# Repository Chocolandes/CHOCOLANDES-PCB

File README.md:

# CHOCOLANDES-PCB

In this repository you will find the gerber files ready for the Chocolandes PCB fabrication and the eagle files with which the pcb was designed.

Here are the components and connections contained in the instrumentacion.sch file:

## Material's list:
### In this project we use two ESP32 microcontrollers. One is dedicated to the stepper motor movement (ESP-MOT) and the other is in charge of all the other functionalities (ESP-MAIN).
### L293D
Dual DC motor driver 

* In1: D33 ESP-MAIN
* In2: D32 ESP-MAIN
* Out1: Red wire motor pump
* Out2: Black wire motor pump
* En1: 5V
* VCC: 5V
* Vss: 12V
* Pin 4 y 5: GND

### HX711
Load cell ADC converter

* E+: Red
* E-: Black
* A+: Withe
* A-: Green
* Dt: D26 ESP-MAIN
* Sck: D27 ESP-MAIN
* Vcc: 5V

### A4988
Stepper motor driver 
* Dir: D19  ESP-MOT
* Step: D18  ESP-MOT
* Enable: D5  ESP-MOT
* Vdd: 5V
* Reset & Sleep Are connected between them
* 2B: Black 
* 2A: Green
* 1A: Blue
* 1B: Red
* Vmot: External power (12V)

### NEMA 17HS4401s
Stepper motor with 1.8° resolution
* Black: 2B
* Green: 2A
* Blue: 1A
* Red: 1B
### HC020P
* Vdd: 5V
* Data: D34 ESP-MOT
### DS18B20
* Vdd: 5V
* Data: D13 ESP-MAIN
### Motor Pump
* Red: Out1 L293D
* Black: Out2 L293D
### Load Cell
* Red: E+
* Black: E-
* Withe: A+
* Green: A-

### ESP-MAIN
* D33: In1 L293D
* D32: In2 L293D
* D26: Dt HX711
* D27: Sck HX711
* D13: Data DS18B20
### ESP-MOT
* D5: Enable A4988
* D19: DIR A4988
* D18: STEP A4988
* D34: Data HC020P

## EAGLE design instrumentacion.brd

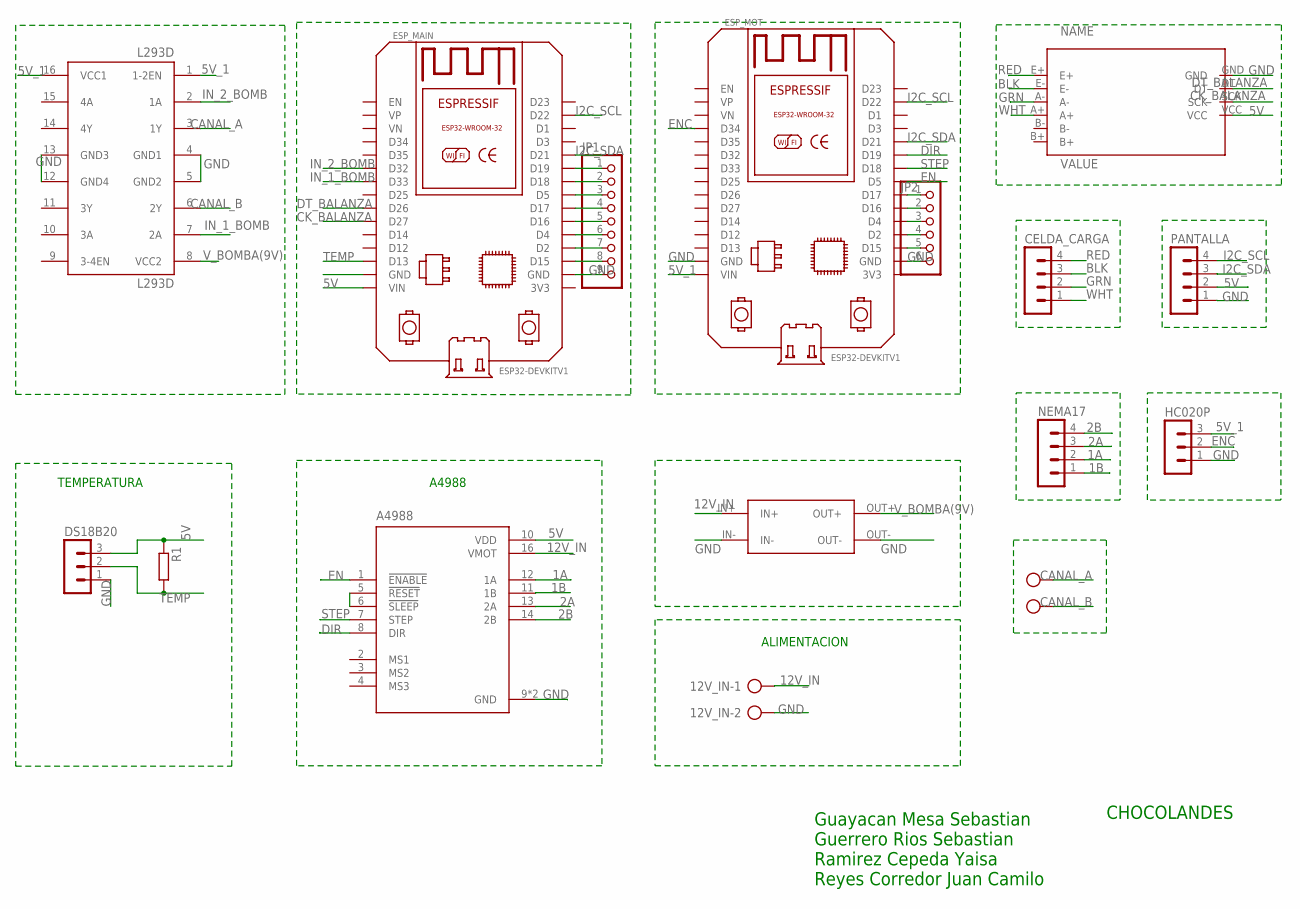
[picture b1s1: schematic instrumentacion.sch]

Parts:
12V_IN: SMKDSP_1,5/2
A4988: A4988_STEPPER_MOTOR_DRIVER_CARRIER; MODULE_A4988_STEPPER_MOTOR_DRIVER_CARRIER
BOMBA: SMKDSP_1,5/2
CELDA_CARGA: MA04-1
DS18B20: MA03-1
ESP_MAIN: ESP32DEVKITV1; ESP32-DEVKITV1
ESP_MOT: ESP32DEVKITV1; ESP32-DEVKITV1
HC020P: MA03-1
HX711: HX711A; HX711
JP1: PINHD-1X9; 1X09
JP2: PINHD-1X6; 1X06
L293D: L293D; DIL16
NEMA17: MA04-1
PANTALLA: MA04-1
R1: R-EU_0204/7; 0204/7
U$1: LM2596_3A; LM259_PADS

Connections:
1A: A4988.12 (1A), NEMA17.2
1B: A4988.11 (1B), NEMA17.1
2A: A4988.13 (2A), NEMA17.3
2B: A4988.14 (2B), NEMA17.4
5V: A4988.10 (VDD), DS18B20.3, ESP_MAIN.VIN, HX711.VCC, PANTALLA.2, R1.1
5V_1: ESP_MOT.VIN, HC020P.3, L293D.1 (1-2EN), L293D.16 (VCC1)
12V_IN: 12V_IN.1, A4988.16 (VMOT), U$1.IN+
BLK: CELDA_CARGA.3, HX711.E-
CANAL_A: BOMBA.1, L293D.3 (1Y)
CANAL_B: BOMBA.2, L293D.6 (2Y)
CK_BALANZA: ESP_MAIN.D27, HX711.SCK
DIR: A4988.8 (DIR), ESP_MOT.D19
DT_BALANZA: ESP_MAIN.D26, HX711.DT
EN: A4988.1 (!ENABLE), ESP_MOT.D5
ENC: ESP_MOT.D34, HC020P.2
GND: 12V_IN.2, A4988.9 (GND), A4988.15 (GND), DS18B20.1, ESP_MAIN.GND, ESP_MAIN.GND@1 (GND), ESP_MOT.GND, ESP_MOT.GND@1 (GND), HC020P.1, HX711.GND, JP1.9, JP2.6, L293D.4 (GND1), L293D.5 (GND2), L293D.12 (GND4), L293D.13 (GND3), PANTALLA.1, U$1.IN-, U$1.OUT-
GRN: CELDA_CARGA.2, HX711.A-
I2C_SCL: ESP_MAIN.D22, ESP_MOT.D22, PANTALLA.4
I2C_SDA: ESP_MAIN.D21, ESP_MOT.D21, PANTALLA.3
IN_1_BOMB: ESP_MAIN.D33, L293D.7 (2A)
IN_2_BOMB: ESP_MAIN.D32, L293D.2 (1A)
unnamed: ESP_MAIN.D19, JP1.1
unnamed: ESP_MAIN.D18, JP1.2
unnamed: ESP_MAIN.D5, JP1.3
unnamed: ESP_MAIN.D17, JP1.4
unnamed: ESP_MAIN.D16, JP1.5
unnamed: ESP_MAIN.D4, JP1.6
unnamed: A4988.5 (!RESET), A4988.6 (!SLEEP)
unnamed: ESP_MAIN.D2, JP1.7
unnamed: ESP_MAIN.D15, JP1.8
unnamed: ESP_MOT.D17, JP2.1
unnamed: ESP_MOT.D16, JP2.2
unnamed: ESP_MOT.D4, JP2.3
unnamed: ESP_MOT.D2, JP2.4
unnamed: ESP_MOT.D15, JP2.5
RED: CELDA_CARGA.4, HX711.E+
STEP: A4988.7 (STEP), ESP_MOT.D18
TEMP: DS18B20.2, ESP_MAIN.D13, R1.2
V_BOMBA(9V): L293D.8 (VCC2), U$1.OUT+
WHT: CELDA_CARGA.1, HX711.A+

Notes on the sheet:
TEMPERATURA
ALIMENTACION
A4988
CHOCOLANDES
Guayacan Mesa Sebastian Guerrero Rios Sebastian Ramirez Cepeda Yaisa Reyes Corredor Juan Camilo

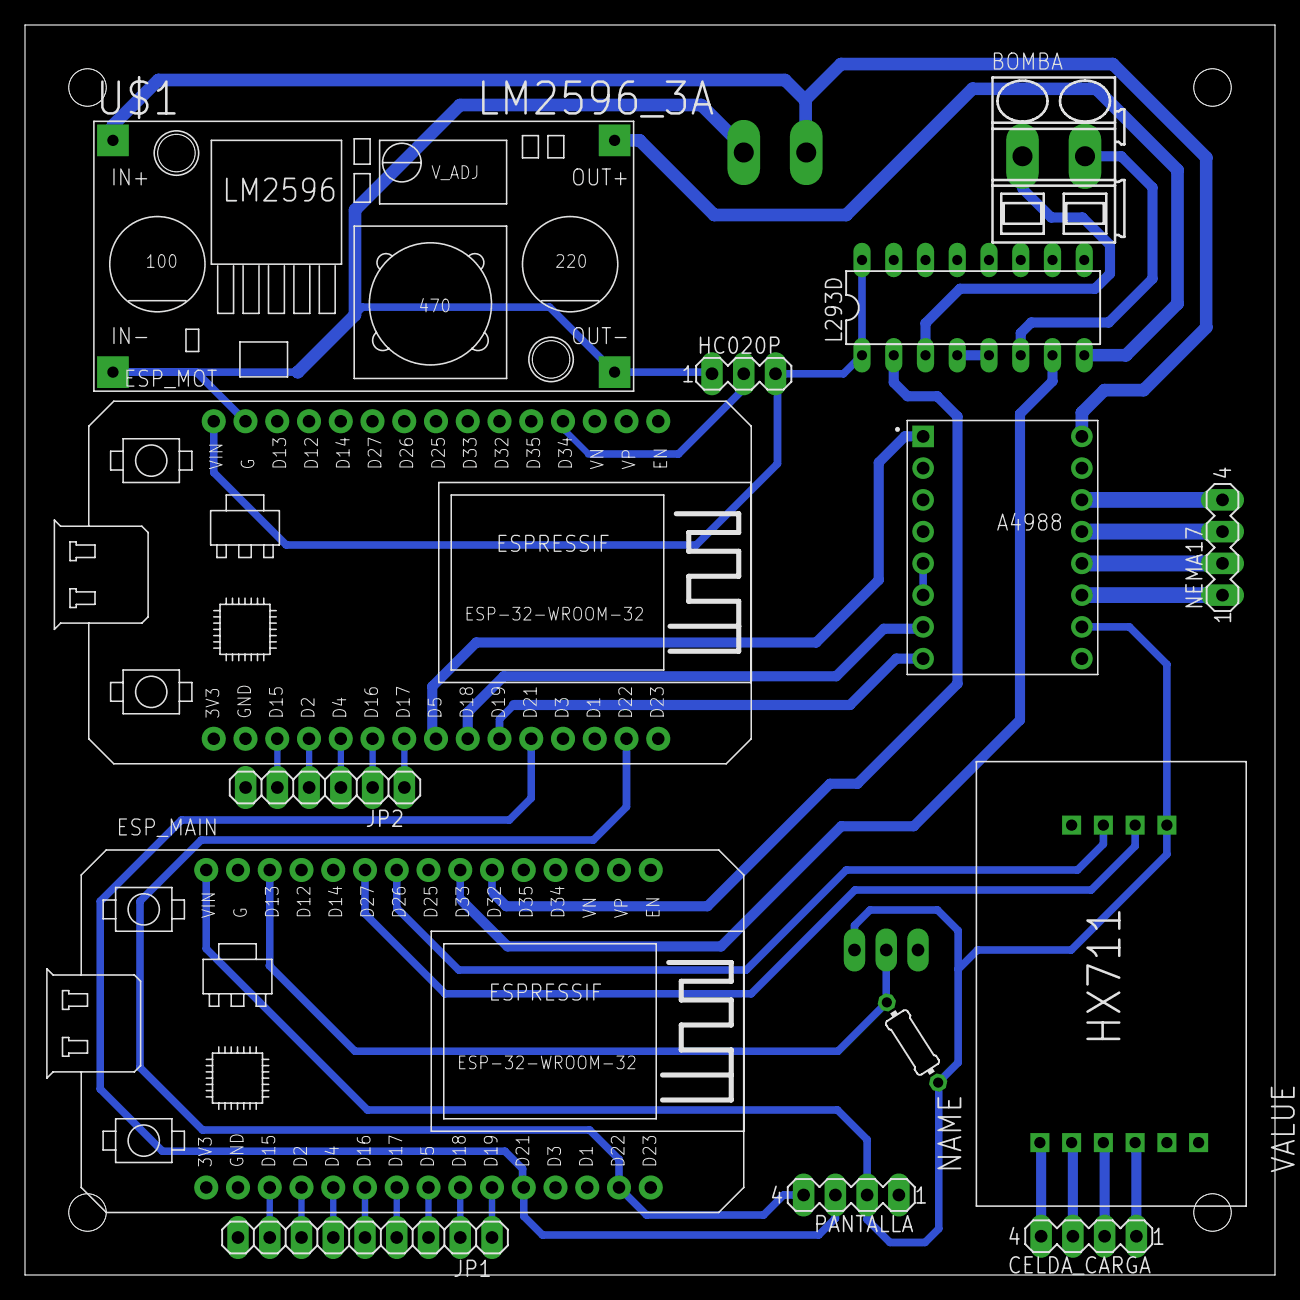
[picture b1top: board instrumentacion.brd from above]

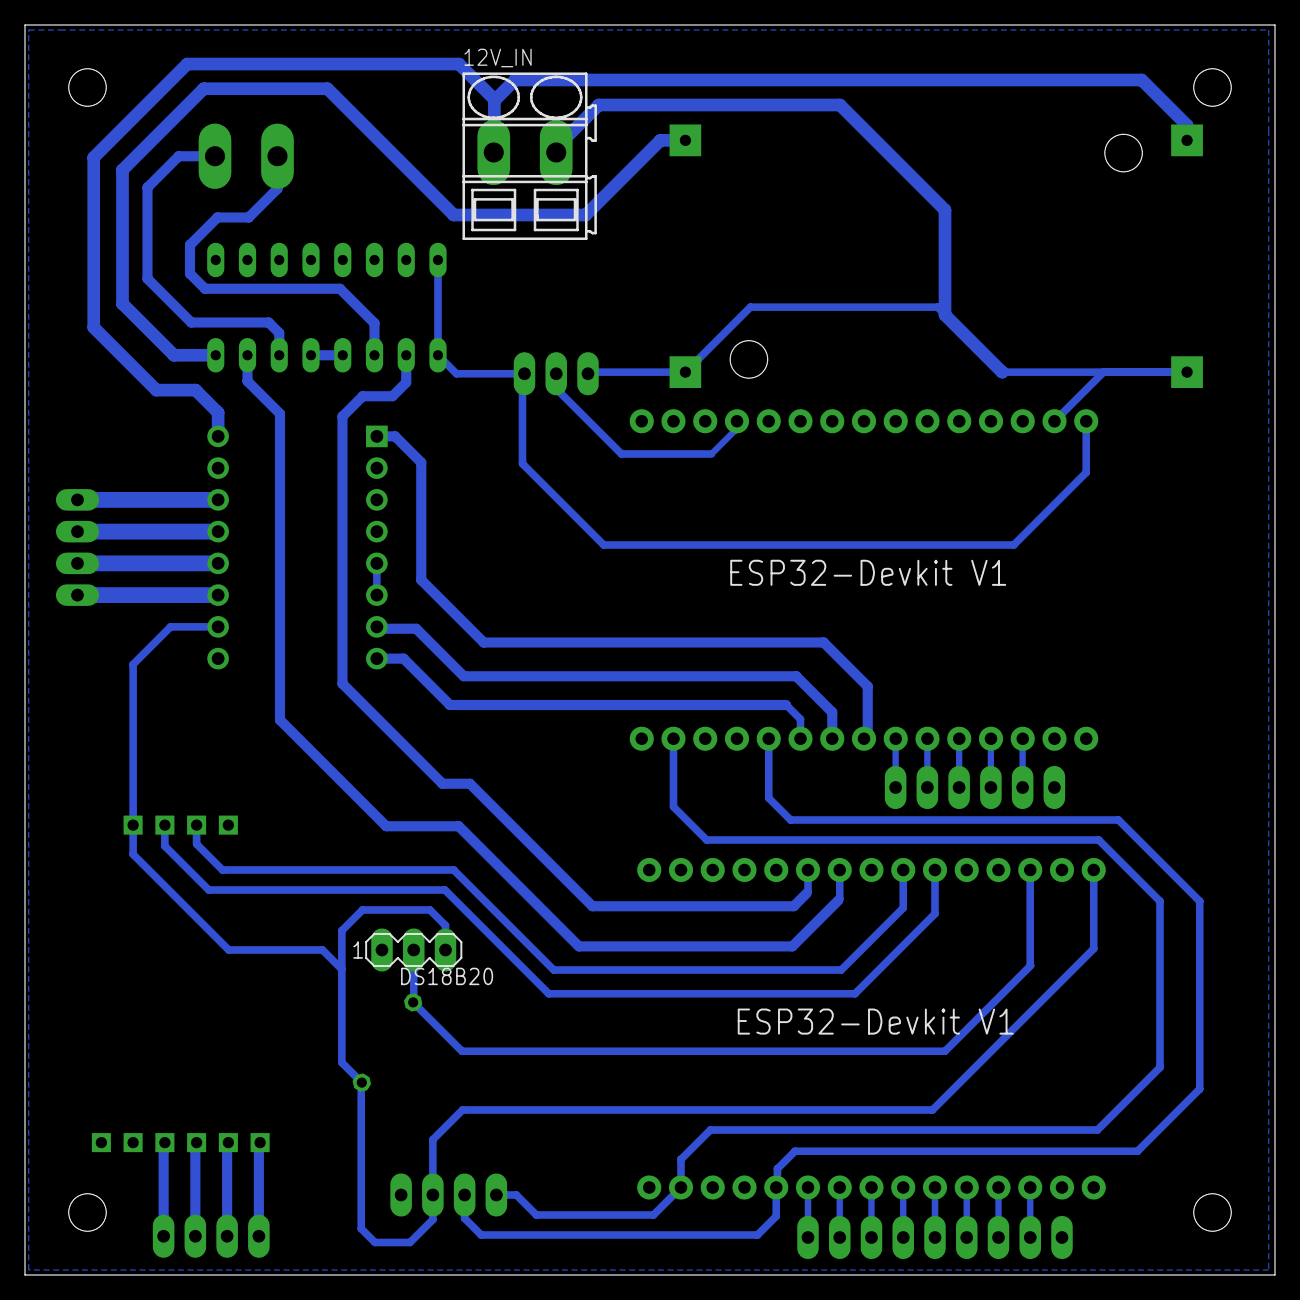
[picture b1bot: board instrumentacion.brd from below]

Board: 2 copper layers, 100.0 x 100.0 mm, 16 parts (2 on the bottom side), 40 nets.
